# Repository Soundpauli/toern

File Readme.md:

# TŒRN `[tɜːn]`

**Open-source sequencer and sampler** — by [warft_ctrl](mailto:info@toern.live)

> Say it like *turn*. As in: turn the knobs. Turn a doodle into a beat. Turn “I can’t play piano” into “wait, that slap though.”

TŒRN is a sequenced musical device for beginners, makers, and anyone who likes blinking lights more than plugin menus. Think **Etch-A-Sketch™ energy**, but instead of drawing a wobbly staircase you draw drums, synths, and happy accidents — on a vivid **32×16 RGB LED panel** (standard; 16×16 optional) that is both the screen *and* the keyboard.

It sits on a Teensy 4.1, runs from a Micro SD card full of your WAVs, and is happy on a desk, in a backpack, or on battery at the park where strangers will ask “what *is* that?”

**Status:** under very active development. Things move fast. Stay tuned, and don’t be surprised if yesterday’s weird bug is today’s charming feature (or the other way around).

---

## What it is (in plain language)

You get:

- **8 sample voices** for drums, one-shots, loops, and “that weird recording from the metro”
- **1 three-voice polyphonic synth** with presets (bass, keys, chiptune, pads… the usual suspects)
- **2 monophonic synths** with LFO and arpeggiator for leads that refuse to sit still
- A **32-step × 8-page** sequencer (256 steps of room to overthink; 16×16 mode uses 16 steps × 16 pages), page chaining into songs, MIDI in/out, filters, bitcrush, reverb, and enough real-time knobs to keep your hands busy and your laptop jealous

No laptop required once it’s built. Samples live on the SD card. Patterns autosave. You twist, tap, and suddenly it’s 2 a.m.

For the friendly guided tour (first beat in about a minute), open the **[handbook](docs/handbook/index.html)** in this repo.

---

## A tiny history

TŒRN builds on the legacy of the **NI404**, with more features, fewer cables dangling off the side, and a custom PCB where everything mounts cleanly. The older “extra boards and hope” era is over.

Meet the glow-up:

- **RGB-I2C rotary encoders** — smoother, prettier, and they light up like they mean it
- **Custom PCB** — codec, charging, and jacks on one board
- **USB-C** — because micro-USB was a character-building experience we no longer need
- **LiPo charging port** — optional battery for true “make beats on a train” energy (battery not included; we trust you with electricity)
- **Proper audio I/O** — 6.35 mm headphone out, line in/out, mic in, *plus* a built-in mic for “sample the room right now” moments
- **TRS MIDI in/out** — play nice with the rest of your setup
- **On/off switch** — underrated luxury
- **Touch buttons** — for the things knobs shouldn’t monopolize
- **Laser-cut acrylic case** — files included; looks finished, not “breadboard cosplay”
- **JST connectors** — expansion leads plug in

Open source as always: schematics, code, and design files are here for you to poke, fork, and improve.

---

## Feature list

### Sequencer

- **11 instrument voices** on a 16-row grid: 8 sample voices (1–8), one 3-voice poly synth (11), two mono synths (13–14)
- Standard **32 steps per page × 8 pages** → 256 steps per pattern; optional 16×16 mode uses 16 steps × 16 pages
- **Voice mode**: each voice keeps its own pattern length. It loops the pages that hold its notes, pitches included, while the other voices keep looping on their own
- **FIRE** (ETC → ADV menu): optional playhead sparks when a chosen voice’s notes light white
- Store up to **999 patterns**, **999 samples**, **999 samplepacks**
- **Autosave / autoload** so your 3 a.m. genius doesn’t vanish at boot
- **Switch patterns live** without stopping playback
- **Song mode**: chain up to **64** page assignments from the current pattern
- Pattern ops: copy/paste, transpose page/channel (±1 octave), smart random notes (major/minor + rhythm ideas), clear page/channel
- **SWAP** exchanges notes between voices, with octave offsets; optional **SUBP** file subpatterns extend arrangements

### Sample voices (channels 1–8)

- Up to **~12 seconds** per voice at 44.1 kHz
- Browse and load samples **while playing** (yes, really)
- Per-voice start/end trim, forward/reverse
- **TIME** stretches or shortens samples independently of pitch
- Samplepacks (including pack 0 = custom per-voice assignment)
- Record from **built-in mic / line-in / mic-in** straight in the sample browser
- Save or merge used samples back to the SD card as a pack

### Synth voices

**Channel 11 — poly synth**

- 3 oscillators per voice × 3 voices
- Presets: BASS, KEYS, CHPT, PAD, WOW, ORG, FLT, LEAD, ARP, BRSS
- Per-voice ADSR, filter envelope, pan, volume, pitch (cents & semitones), waveform

**Channels 13–14 — mono synths**

- 2 oscillators each
- ADSR, LFO on cutoff/resonance, MIDI arpeggiator (step/span; does not pitch-shift grid notes)
- Waveforms: sine, saw, square, triangle

### Effects (all channels)

- **ADSR** — attack / decay / sustain / release (0–32 range)
- **Bitcrusher** — bit depth 1–16 (0 = bypass), sample-rate reduction down to glorious crunch
- **Filter** — LP / HP / BP, 0–10 kHz, resonance 0.7–5.0, smooth transitions
- **Reverb** — room size, damping, wet/dry; denser six-comb/four-diffuser network on reverb-equipped voices
- Fast filter access on encoder #3 during runtime (assignable default per channel)

### MIDI, clock & extras

- TRS MIDI in/out, clock send/receive, notes, transport
- BPM **40–300**, internal clock, external MIDI clock, tap tempo via touch
- Live recording / looping (touch-hold), up to ~12 s per voice
- Note probability, velocity, condition triggers (those “only every other bar” tricks)
- Global transpose, per-channel detune & octave, fine cents on the poly synth
- Mute / solo, pattern modes (OFF, ON, SONG, NEXT)
- Stereo routing options
- USB **Audio + Serial**: send the mix to a computer while using the SD tool; musical MIDI uses the TRS ports
- Analog clock **out (J25)**, clock **in (J26)** and voice-triggered **sidechain out (J27)**
- **TOUCHY** performance pads, live fills, and per-voice audition
- Browser tools for firmware flashing, SD transfers, sample conversion and the simulator
- **Demo animation:** open **ETC → INFO**, press **touch3 / BUTTON_C**; press and release **Touch 1 / BUTTON_A** to return to INFO

---

## Tech specs

| | |
|---|---|
| **Brain** | Teensy 4.1, PSRAM fitted. Audio codec is the SGTL5000 on the carrier |
| **Memory** | 16 MB PSRAM target; Micro SD (handbook suggests up to 64 GB, SanDisk Ultra) |
| **Audio** | 44.1 kHz, 16-bit mono WAV |
| **Controls** | 4× RGB illuminated I2C rotary-push encoders, 5 capacitive touch buttons |
| **Display** | Standard [32×16 RGB LED panel](https://de.aliexpress.com/item/1005010071864259.html), 512 LEDs (FastLED); 16×16 optional |
| **I/O** | 6.35 mm headphones, line in/out, mic in; built-in mic; TRS MIDI in/out |
| **Power** | USB-C or optional LiPo + charging |

---

## Repo map (where stuff lives)

| Path | Contents |
|------|----------|
| `platformio/` | Arduino sketch tabs, headers, custom audio in `src/`, build scripts and `platformio.ini` |
| `hardware/PCB/` | KiCad boards, schematics, manufacturing files and [purchasing BOMs](hardware/PCB/BOM/README.md) |
| `hardware/housing/` | Fusion archives, laser DXFs and panel previews |
| `docs/devdocs/` | Developer documentation → [docs.toern.live](https://docs.toern.live/) |
| `docs/handbook/` | Operator handbook → [handbook.toern.live](https://handbook.toern.live/) |
| `docs/BUILD.md`, `docs/info.md` | Hardware assembly and firmware build instructions |
| `tools/firmware/` | Browser firmware flasher (GPL-3.0) |
| `tools/sdtool/` | Browser SD tool |
| `tools/sim/` | Browser simulator |
| `tools/audioconvert/` | Standalone sample converter |
| `tools/case/` | Standalone case generator; `case.toern.live` planned, not deployed |
| `tools/colorsheme/`, `tools/_shared/` | Color editor and shared tool assets |
| `_debug/` | Host tests, analysis scripts and local diagnostic captures |
| `_private/` | Local business data/helpers; annotation tool in `_private/helpers/annotate/` |
| `website/` | Public project website only; local/deploy-only |

See [the complete directory map](docs/REPOSITORY_LAYOUT.md) for local-only items marked `***`.

Build from the repository root with `pio run -d platformio`, or `cd platformio` first.

For a personal hardware build, follow the [assembly and laser-cutting guide](docs/BUILD.md).
Start with the [BOM directory](hardware/PCB/BOM/README.md): check assembly-part stock
before ordering the PCB. The [pre-order list](hardware/PCB/BOM/preorder-parts.csv)
lists parts to secure for JLCPCB assembly. Then buy the
Teensy, PSRAM, encoders, matrix, cables and
case hardware separately. The website’s **Build** chapter covers the same assembly order.

---

## External libraries & modifications

This project leans on several libraries. Some are stock; some got lovingly (and necessary-ly) poked.

### Modified

- **ResamplingReader.h** (`teensy-variable-playback`)
  Variable rates, interpolation, multi-channel, loop types (repeat / ping-pong), crossfading — in `platformio/src/resamplerReader.h`

- **Treeverb** (`effect_treeverb`)
  Full-rate reverb with balanced 6/4 diffusion in RAM1 — `platformio/src/effect_treeverb.*`; the older `effect_freeverb_dmabuf` remains a host-test reference.

- **FastLED**
  `FASTLED_ALLOW_INTERRUPTS 0` so LEDs and audio don’t argue mid-beat; custom `FastLEDshow()` / `FastLEDclear()` wrappers

- **MIDI**
  Bigger Serial8 buffers for dense clock traffic (`RX 2048`, `TX 128`) and custom TRS MIDI settings

### Standard / upstream

- **TeensyPolyphony** by Nic Newdigate — polyphonic heart of the thing
- **Audio Library** (PJRC)
- **WS2812Serial**, **i2cEncoderLibV2**, **FastTouch**

---

## Get one

Order a TŒRN at **[toern.live](https://toern.live/)**. Questions go to **info@toern.live**.

When it arrives, open the **[handbook](docs/handbook/index.html)** and start at First beat. Power is USB-C. A battery and a microSD card are not in the parcel; the buy page and the handbook hardware chapter name what to get.

Firmware changes: [`info.md`](docs/info.md) to flash, [`docs/devdocs/`](docs/devdocs) for how the code is shaped, [`firmware-edits`](docs/devdocs/docs/contributing/firmware-edits.md) for a new menu page. Fabricating a board from the design files is [`BUILD.md`](docs/BUILD.md) — that is not how a TŒRN is ordered.

---

## License

- **Software / code**: [MIT](LICENSE) — free for personal and commercial use.
- **Firmware loader** (`tools/firmware/`): [GPL-3.0](tools/firmware/LICENSE), because that tool is Teensy Loader Javascript. GPL-3.0 applies only to that folder.
- **Hardware design files** (schematics, PCB layouts, Gerbers, housings, etc.): [CC BY-NC 4.0](https://creativecommons.org/licenses/by-nc/4.0/) — personal / non-commercial use and modification. **Jan-Peter Kuntoff is the only person authorized to sell TŒRN hardware** (bare PCB, assembled PCB, kit, or unit), including boards sold **without a Teensy**. Teensy 4.1 is PJRC’s; it is not licensed in this repo. Anyone else needs written consent to sell.

Commercial hardware licensing: Jan aka **warft_ctrl** — info@toern.live (Hamburg, Germany)

---

## Thank you

Huge thanks to **Paul Stoffregen** and the PJRC crew for Teensy, to the wider open-source audio community, and an especially loud shoutout to **Nic Newdigate** for teensy-polyphony — basically the soul of this project.

Made with too many late nights and exactly the right number of RGB LEDs.

**Jan aka warft_ctrl** (formerly soundpauli)
Hamburg, 2026

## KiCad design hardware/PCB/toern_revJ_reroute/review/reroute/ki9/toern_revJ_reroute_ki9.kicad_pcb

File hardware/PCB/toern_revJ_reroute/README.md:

# Toern revJ reroute

Open `toern_revJ_reroute.kicad_pro` with Backplane KiCad 10.99.0-bp.12.5. This is the archived partial reroute, with 22 nets changed. Its board format requires the newer editor. The original `../toern_revJ` is the stock KiCad 9.0.5 version restored from commit `ab3ea41`.

The [validation summary](review/reroute/validation-summary.md) records results and remaining USB and thermal work. The [pre-restore checkpoint](review/reroute/baseline) preserves the active revJ files from before the restore. The [Specctra session and KiCad 9 seed files](review/reroute/ki9) are an unverified transfer attempt.

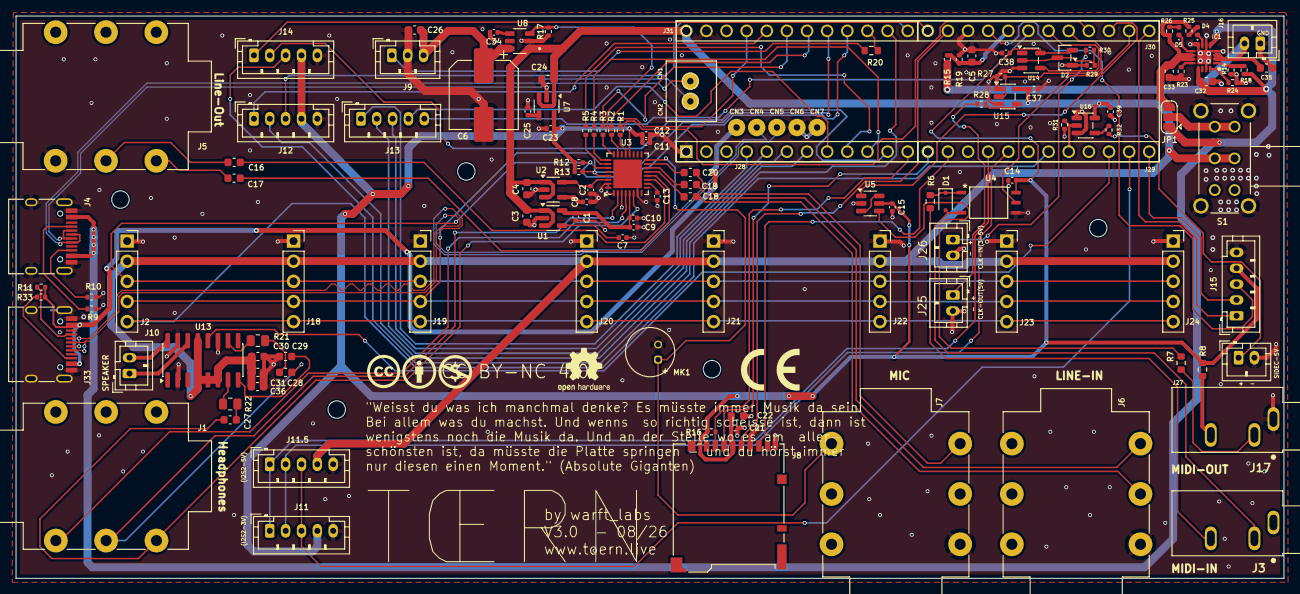
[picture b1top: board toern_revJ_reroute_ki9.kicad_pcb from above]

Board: 4 copper layers, 160.0 x 71.0 mm, 138 parts (0 on the bottom side), 109 nets.

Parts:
C1, C2, C9, C12, C23: 1u; C_0402_1005Metric
C3, C4, C16, C17, C18, C19, C20, C22, C24, C32: 10u; C_0603_1608Metric
C5, C26, C29: 100nF; C_0603_1608Metric
C6: 1000uF; CP_Elec_8x10.5
C7, C8, C25, C37, C38, C39: 100nF; C_0402_1005Metric
C10, C11, C14, C15, C21: 100n; C_0402_1005Metric
C13: 150n; C_0402_1005Metric
C27, C28: 0.47uF; C_0603_1608Metric
C30, C31: 1uF; C_0603_1608Metric
C33, C35: 4.7uF; C_0603_1608Metric
C34: 10nF; C_0402_1005Metric
C36: 22µF; C_0603_1608Metric
CN1, CN2: YZP0354-20100-01
CN3, CN4, CN5, CN6, CN7: YZP0354-20100-01; YZP0354-20100-01_Host
D1: BAT54J; D_SOD-323F
D2: BAT54S; SOT-23
D4: Red; LED_0402_1005Metric
D5: Yellow; LED_0402_1005Metric
IC1: BQ24075TRGTR; QFN50P300X300X100-17N-D
J1, J5, J6, J7: AudioJack3_Switch; Jack_6.35mm_Neutrik_NMJ6HCD2_Horizontal
J2, J18, J19, J20, J21, J22, J23, J24: Conn_01x05_Socket; PinSocket_1x05_P2.54mm_Vertical
J3, J17: AudioJack3_Ground; CUI_SJ1-3533
J4, J33: USB_C_Receptacle_USB2.0; USB_C_Receptacle_HRO_TYPE-C-31-M-12
J8: Micro_SD_Card; microSD_HC_Hirose_DM3BT-DSF-PEJS
J9: Conn_01x03; JST_PH_B3B-PH-K_1x03_P2.00mm_Vertical
J10, J16, J25, J26, J27: Conn_01x02; JST_PH_B2B-PH-K_1x02_P2.00mm_Vertical
J11, J11.5, J12, J13, J14, J15: Conn_01x05; JST_PH_B5B-PH-K_1x05_P2.00mm_Vertical
J28, J29, J30, J31: 929870-01-12-RA; 3M_929870-01-12-RA_Assembly
JP1: SolderJumper_3_Open; SolderJumper-3_P1.3mm_Open_RoundedPad1.0x1.5mm
LOGOOPENHARDWARE: OSHW-Logo2_7.3x6mm_SilkScreen
MK1: Microphone_Condenser; MIC-TH_BD6.0-P1.90-D0.4-L-FD
MountingHole1, MountingHole2, MountingHole3, MountingHole4, MountingHole5: MountingHole_2.2mm_M2
R1, R2, R3, R4, R5: 22R; R_0402_1005Metric
R6, R20: 220R; R_0603_1608Metric
R7, R8: 33R; R_0603_1608Metric
R9, R10: 5.1k; R_0402_1005Metric
R11, R33: 56k; R_0402_1005Metric
R12, R13, R16, R17: 10k; R_0402_1005Metric
R14: 49.9k; R_0402_1005Metric
R15: 1M; R_0402_1005Metric
R18: 200k; R_0402_1005Metric
R19: 1.5M; R_0402_1005Metric
R21, R22: 20k; R_0805_2012Metric
R23: 1.1k; R_0402_1005Metric
R24: 590R; R_0402_1005Metric
R25, R26: 1.5k; R_0402_1005Metric
R27, R29, R31: 100k; R_0402_1005Metric
R28, R32: 1k; R_0402_1005Metric
R30: 22k; R_0402_1005Metric
S1: EG2219
U1, U7: SPX3819M5-L-3-3; SOT-23-5
U2: SPX3819M5-L-1-8; SOT-23-5
U3: SGTL5000XNBA3; QFN-32-1EP_5x5mm_P0.5mm_EP3.6x3.6mm
U4: TLP2361V4_E; 5pin SO6_TOS
U5: 74LVC2G14; SOT-23-6
U6: Teensy4.1; Teensy41
U8: TPS22918DBVR; SOT95P280X145-6N
U13: PAM8403D; SOIC-16_3.9x9.9mm_P1.27mm
U14: 74LVC1G17; SOT-23-5
U15, U16: 74AHCT1G125; SOT-23-5

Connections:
2_OUT2: J13.1, U6.4 (2_OUT2)
3_LRCLK2: J13.3, U6.5 (3_LRCLK2)
4_BCLK2: J13.2, U6.6 (4_BCLK2)
5V-HOST: CN3.1 (CONTACT), J33.A4 (VBUS), J33.A9 (VBUS), J33.B4 (VBUS), J33.B9 (VBUS), R11.2, R33.2
5_IN2: J12.2, U6.7 (5_IN2)
6_OUT1D: J13.4, U6.8 (6_OUT1D)
7_RX2_OUT1A: R5.1, U6.9 (7_RX2_OUT1A)
8_TX2_IN1: R4.1, U6.10 (8_TX2_IN1)
9_OUT1C: J14.2, U6.11 (9_OUT1C)
10_CS_MQSR: J8.2 (DAT3/CD), R16.1, U6.12 (10_CS_MQSR)
11_MOSI_CTX1: J8.3 (CMD), U6.13 (11_MOSI_CTX1)
12_MISO_MQSL: J8.7 (DAT0), U6.14 (12_MISO_MQSL)
13_SCK_LED: J8.5 (CLK), U6.35 (13_SCK_LED)
14_A0_TX3_SPDIF_OUT: J14.1, U6.36 (14_A0_TX3_SPDIF_OUT)
15_A1_RX3_SPDIF_IN: J12.3, U6.37 (15_A1_RX3_SPDIF_IN)
16_A2_RX4_SCL1: J14.3, U6.38 (16_A2_RX4_SCL1)
17_A3_TX4_SDA1: R20.2, U6.39 (17_A3_TX4_SDA1)
18_A4_SDA: J2.3, J18.3, J19.3, J20.3, J21.3, J22.3, J23.3, J24.3, R12.2, U3.27 (CTRL_DATA), U6.40 (18_A4_SDA)
19_A5_SCL: J2.4, J18.4, J19.4, J20.4, J21.4, J22.4, J23.4, J24.4, R13.2, U3.29 (CTRL_CLK), U6.41 (19_A5_SCL)
20_A6_TX5_LRCLK1: R2.1, U6.42 (20_A6_TX5_LRCLK1)
21_A7_RX5_BCLK1: R3.1, U6.43 (21_A7_RX5_BCLK1)
22_A8_CTX1: J12.1, U6.44 (22_A8_CTX1)
23_A9_CRX1_MCLK1: R1.1, U6.45 (23_A9_CRX1_MCLK1)
24_A10_TX6_SCL2: J11.1, J11.5.1, U6.16 (24_A10_TX6_SCL2)
25_A11_RX6_SDA2: J11.2, J11.5.2, U6.17 (25_A11_RX6_SDA2)
27_A13_SCK1: J2.5, J18.5, J19.5, J20.5, J21.5, J22.5, J23.5, J24.5, U6.19 (27_A13_SCK1)
28_RX7: R31.2, U6.20 (28_RX7), U16.2
30_CRX3: U6.22 (30_CRX3), U13.12 (~SHDN)
31_CTX3: J11.3, J11.5.3, U6.23 (31_CTX3)
32_OUT1B: J15.2, U6.24 (32_OUT1B)
33_MCLK2: J15.1, U6.25 (33_MCLK2)
34_RX8: U4.5, U6.26 (34_RX8)
35_TX8: U5.1, U6.27 (35_TX8)
36_CS: R17.2, U6.28 (36_CS), U8.3 (ON)
37_CS: R27.2, U6.29 (37_CS), U15.2
38_CS1_IN1: U6.30 (38_CS1_IN1), U14.4
39_MISO1_OUT1A: J13.5, U6.31 (39_MISO1_OUT1A)
40_A16: C5.2, R15.2, R19.2, U6.32 (40_A16)
41_A17: J15.3, U6.33 (41_A17)
+1V8: C2.1, U2.5 (OUT), U3.30 (VDDD)
+3.3V: C11.1, C12.1, C14.2, C15.1, C21.2, C22.1, C23.1, C38.1, D2.2 (K), J8.4 (VDD), J11.4, J12.4, J14.4, J15.4, R8.2, R12.1, R13.1, R16.2, U3.20 (VDDIO), U4.6 (vcc), U5.5 (VCC), U7.5 (OUT), U14.5 (VCC)
+3.3VA: C1.1, C9.1, C10.1, U1.5 (OUT), U3.5 (VDDA)
+5V: C3.1, C4.1, C24.1, C30.2, C31.1, C36.1, C37.2, C39.2, J2.2, J11.5.4, J18.2, J19.2, J20.2, J21.2, J22.2, J23.2, J24.2, S1.2 (COM_1), S1.5 (COM_2), U1.1 (IN), U1.3 (EN), U2.1 (IN), U2.3 (EN), U6.48 (VIN), U7.1 (IN), U7.3 (EN), U8.1 (VIN), U13.4 (PVDD), U13.5 (~MUTE), U13.6 (VDD), U13.13 (PVDD), U15.5 (VCC), U16.5 (VCC)
D+: CN2.1 (CONTACT), J4.A6 (D+), J4.B6 (D+)
D+HOST: CN5.1 (CONTACT), J33.A6 (D+), J33.B6 (D+)
D-: CN1.1 (CONTACT), J4.A7 (D-), J4.B7 (D-)
D-HOST: CN4.1 (CONTACT), J33.A7 (D-), J33.B7 (D-)
GND: C1.2, C2.2, C3.2, C4.2, C5.1, C6.2, C7.2, C8.2, C9.2, C10.2, C11.2, C12.2, C13.2, C14.1, C15.2, C21.1, C22.2, C23.2, C24.2, C25.2, C26.2, C29.1, C30.1, C31.2, C32.2, C33.2, C34.2, C35.2, C36.2, C37.1, C38.2, C39.1, CN6.1 (CONTACT), CN7.1 (CONTACT), D2.1 (A), IC1.4 (~CE), IC1.6 (EN1), IC1.8 (VSS), IC1.15 (SYSOFF), IC1.17 (EP), J2.1, J4.A1 (GND), J4.A12 (GND), J4.B1 (GND), J4.B12 (GND), J4.S1 (SHIELD), J5.S, J6.S, J7.S, J8.6 (VSS), J8.9 (SHIELD), J9.2, J11.5, J11.5.5, J12.5, J14.5, J15.5, J16.1, J17.1, J18.1, J19.1, J20.1, J21.1, J22.1, J23.1, J24.1, J25.2, J26.2, J27.2, J33.A1 (GND), J33.A12 (GND), J33.B1 (GND), J33.B12 (GND), J33.S1 (SHIELD), MK1.2 (-), R9.2, R10.2, R14.2, R17.1, R19.1, R23.2, R24.2, R27.1, R29.1, R31.1, S1.MH1, S1.MH2, S1.MH3, S1.MH4, U1.2 (GND), U2.2 (GND), U3.1 (GND), U3.3 (GND), U3.7 (AGND), U3.31 (CTRL_ADR0_CS), U3.32 (CTRL_MODE), U3.33 (GND), U4.4 (gnd), U5.2 (GND), U6.1 (GND), U6.34 (GND), U6.47 (GND), U7.2 (GND), U8.2 (GND), U13.2 (PGND), U13.11 (GND), U13.15 (PGND), U14.3 (GND), U15.1, U15.3 (GND), U16.1, U16.3 (GND)
LINEIN_L: C19.2, U3.14 (LINEIN_L)
LINEIN_R: C18.2, U3.13 (LINEIN_R)
MIC: C20.2, U3.15 (MIC)
MICBIAS: J7.TN, MK1.1 (+), U3.16 (MIC_BIAS)
unnamed: C16.2, J5.R
unnamed: C17.2, J5.T
unnamed: C18.1, J6.R
unnamed: C19.1, J6.T
unnamed: C20.1, J7.T
unnamed: C27.2, R22.1
unnamed: C28.2, R21.1
unnamed: D1.2 (A), J3.2, U4.3
unnamed: D1.1 (K), R6.1, U4.1
unnamed: D2.3 (common), R29.2, R30.2, U14.2
unnamed: D4.2 (A), R25.1
unnamed: D4.1 (K), IC1.7 (~PGOOD)
unnamed: D5.2 (A), R26.1
unnamed: D5.1 (K), IC1.9 (~CHG)
unnamed: IC1.12 (ILIM), R23.1
unnamed: IC1.16 (ISET), R24.1
unnamed: IC1.1 (TS), R14.1, R18.1
unnamed: J3.3, R6.2
unnamed: J4.A5 (CC1), R9.1
unnamed: J4.B5 (CC2), R10.1
unnamed: J9.1, R20.1
unnamed: C6.1, C26.1, J9.3, U8.6 (VOUT)
unnamed: J10.1, U13.14 (ROUT-)
unnamed: J10.2, U13.16 (ROUT+)
unnamed: J17.2, R7.2
unnamed: J17.3, R8.1
unnamed: J25.1, R28.1
unnamed: J26.1, R30.1
unnamed: J27.1, R32.1
unnamed: J33.A5 (CC1), R11.1
unnamed: J33.B5 (CC2), R33.1
unnamed: JP1.2 (C), S1.3 (NO_1), S1.4 (NO_2)
unnamed: R7.1, U5.4
unnamed: R28.2, U15.4
unnamed: R32.2, U16.4
unnamed: C7.1, U1.4 (BP)
unnamed: C8.1, U2.4 (BP)
unnamed: C27.1, J1.T, U3.6 (HP_L)
unnamed: C28.1, J1.R, U3.2 (HP_R)
unnamed: J1.S, U3.4 (HP_VGND)
unnamed: R5.2, U3.26 (I2S_DIN)
unnamed: R4.2, U3.25 (I2S_DOUT)
unnamed: R2.2, U3.23 (I2S_LRCLK)
unnamed: R3.2, U3.24 (I2S_SCLK)
unnamed: C17.1, U3.12 (LINEOUT_L)
unnamed: C16.1, U3.11 (LINEOUT_R)
unnamed: R1.2, U3.21 (SYS_MCLK)
unnamed: C13.1, U3.10 (VAG)
unnamed: U5.3, U5.6
unnamed: C25.1, U7.4 (BP)
unnamed: C34.1, U8.4 (CT)
unnamed: R22.2, U13.7 (INL)
unnamed: R21.2, U13.10 (INR)
unnamed: C29.2, U13.8 (VREF)
VBAT: C35.1, IC1.2 (BAT_1), IC1.3 (BAT_2), J16.2, R15.1
VBUS: C32.1, IC1.5 (EN2), IC1.13 (IN), J4.A4 (VBUS), J4.A9 (VBUS), J4.B4 (VBUS), J4.B9 (VBUS), JP1.1 (A), R18.2
VYS: C33.1, IC1.10 (OUT_1), IC1.11 (OUT_2), JP1.3 (B), R25.2, R26.2

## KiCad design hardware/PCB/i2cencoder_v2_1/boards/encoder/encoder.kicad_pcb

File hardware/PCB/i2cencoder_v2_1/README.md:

# DuPPa I2C Encoder V2.1 for TŒRN

Open [encoder.kicad_pro](boards/encoder/encoder.kicad_pro) for the standalone four-layer KiCad project. The PCB preserves the DuPPa module outline, header and encoder drill geometry and adds a component-side TC2030-PKT-NL ICSP connection. See the [layout and validation report](review/layout.md) for the KiCad 9-format export, electrical checks and board renders.

The materials in [extra/upstream](extra/upstream) are pinned to DuPPa commit `d47fd5afe6d1130eee8f7d02c4856071b2adc8be`. They include the original hardware release and upstream license. Firmware source and both published HEX images are available through [pinned upstream links](extra/upstream/Firmware/README.md), rather than redistributed here. [DuPPa repository](https://github.com/DuPPadotnet/I2CEncoderV2.1/tree/d47fd5afe6d1130eee8f7d02c4856071b2adc8be) · [CircuitMaker project](https://workspace.circuitmaker.com/Projects/Details/Simone--Caron/I2C-Encoder-V2)

## Licensing

Hardware and the KiCad/ICSP modifications: **GPLv3**. Documentation: **CC BY-SA 4.0**. Original design by **DuPPa / Simone Caron**; TŒRN adaptations by Jan-Peter Kuntoff, recorded 2026-11-19. This folder is excluded from TŒRN’s MIT and noncommercial hardware defaults and exclusive-commercial-sale restriction. See [NOTICE.md](NOTICE.md) for attribution, modification details and license scope, and [LICENSE](LICENSE) for GPLv3.

## ICSP connector

Use the standard six-pad TC2030 no-legs pattern with the **TC2030-PKT-NL** cable for PICkit 3, 4 or 5. The TC2030-MCP-NL uses the same board geometry and ICSP assignment with an RJ12 programmer end. J1 implements the standard geometry on the component side with the numbered contacts connected as shown below. [Direct PICkit cable](https://www.tag-connect.com/product/tc2030-pkt-nl-6-pin-no-legs-cable-for-microchip-pickit-3) · [Tag-Connect pattern and wiring](https://www.tag-connect.com/wp-content/uploads/bsk-pdf-manager/2022/06/TC2030-MCP-NL.pdf)

| Pad | ICSP signal | DuPPa connection |
|---:|---|---|
| 1 | MCLR / VPP | U1 pin 1, RA3 / ADD3, MCU side of SJ4 |
| 2 | VDD target | U1 pin 18, VDD, MCU side of ferrite L1 |
| 3 | GND | U1 pin 17 and exposed pad GND net |
| 4 | PGD / ICSPDAT | U1 pin 16, RA0 / ADD0, MCU side of SJ1 |
| 5 | PGC / ICSPCLK | U1 pin 15, RA1 / ADD1, MCU side of SJ2 |
| 6 | AUX | Leave open |

J1 has three 0.9906 mm non-plated guide holes, six 0.7874 mm mask-open pads with no paste, and 1.27 mm contact spacing. The PCB has rule areas for the contact gap and nearby pours. The silkscreen dot identifies pin 1. Keep the module off the carrier while attaching the programming cable. [DuPPa hardware schematic and PCB drawing](https://github.com/DuPPadotnet/I2CEncoderV2.1/blob/master/Hardware/EncoderI2Cv2.1Layer.pdf) · [Microchip programming specification](https://ww1.microchip.com/downloads/aemDocuments/documents/OTH/ProductDocuments/ProgrammingSpecifications/40001738D.pdf)

## Flash sequence

A blank PIC16F18345 needs programming. Use MPLAB IPE with device PIC16F18345 and a PICkit, select the upstream [REV2.3 production HEX](https://github.com/DuPPadotnet/I2CEncoderV2.1/blob/d47fd5afe6d1130eee8f7d02c4856071b2adc8be/Firmware/Binary%20file%20REV2.3/I2CEncoderV2.1.X.production.hex), and program and verify flash and configuration words. Program with the module disconnected from the TŒRN carrier and with SJ1, SJ2 and SJ4 open. Power the target from one source and have the programmer reference the target VDD through pad 2. Use high-voltage ICSP, which is required to write the image's disabled LVP configuration. Set the address jumpers only after programming. Reopen any of SJ1, SJ2 or SJ4 that were closed before reprogramming the module.

Both upstream HEX files passed every Intel HEX record checksum and have LVP cleared in CONFIG3. The newer published REV2.3 file is the proposed first-article image. There has been no hardware flash or verification yet. [Upstream firmware notes](https://github.com/DuPPadotnet/I2CEncoderV2.1/tree/master/Firmware) · [Microchip programming specification](https://ww1.microchip.com/downloads/aemDocuments/documents/OTH/ProductDocuments/ProgrammingSpecifications/40001738D.pdf)

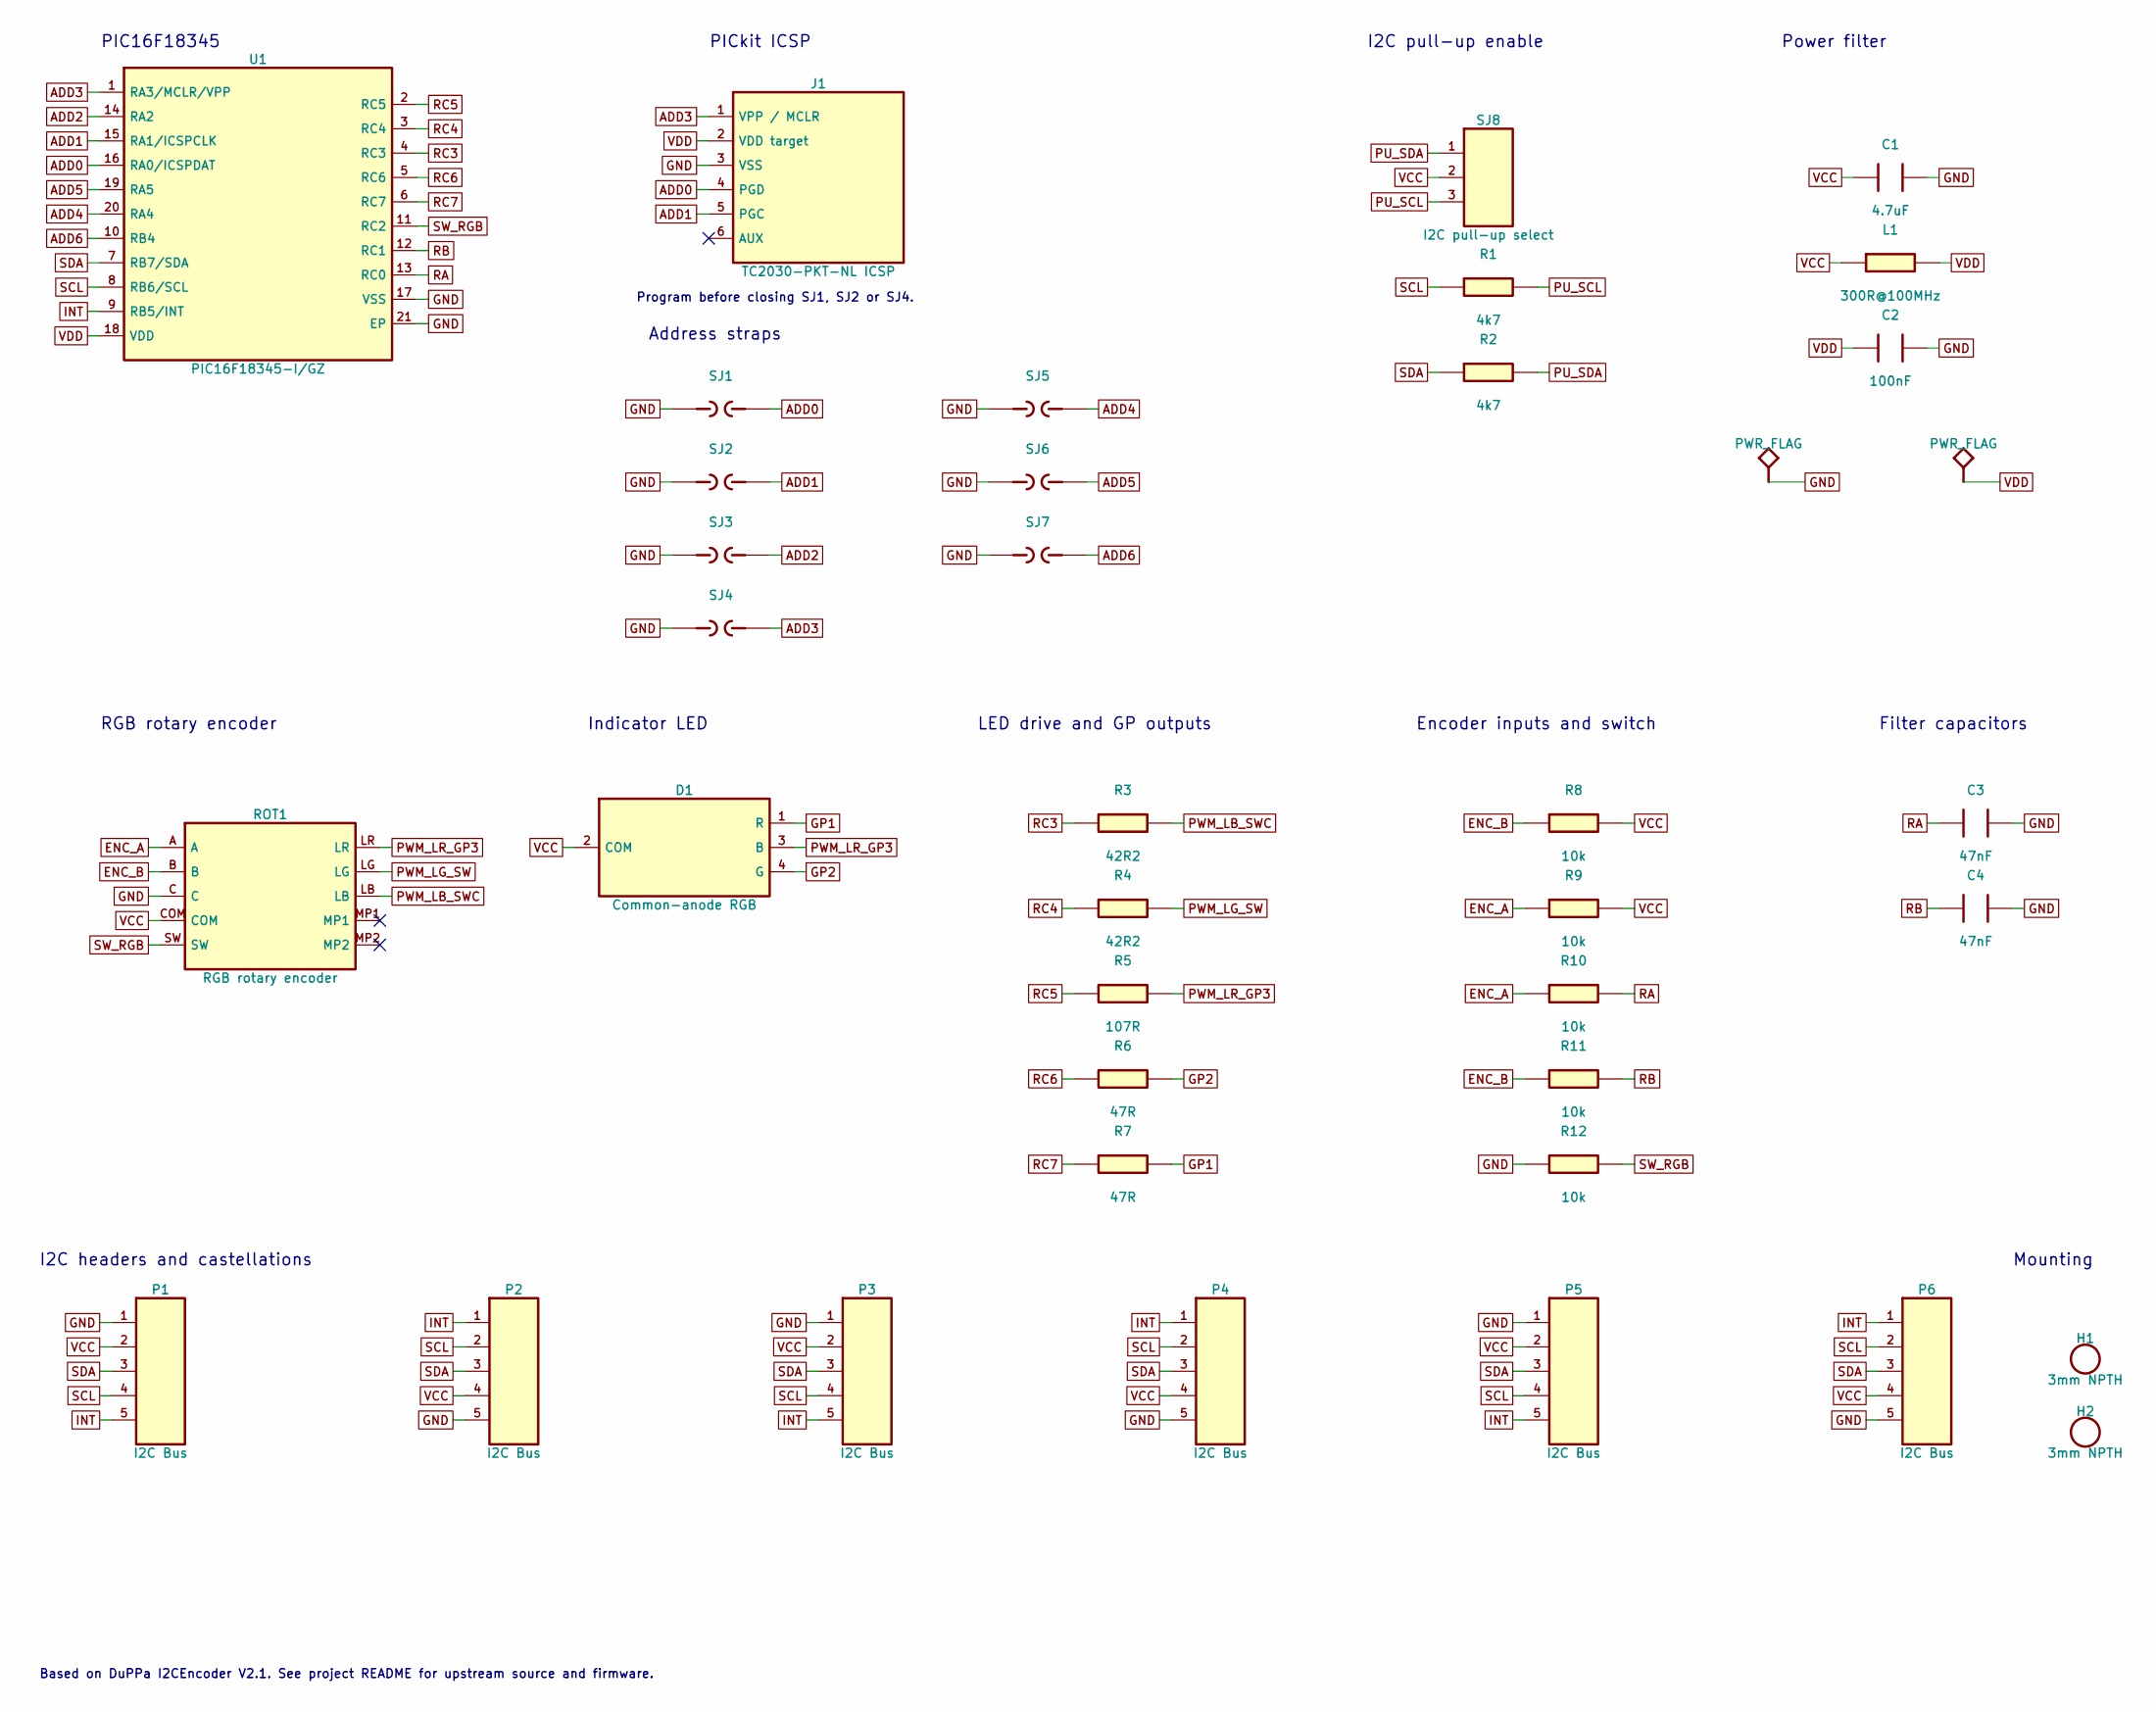
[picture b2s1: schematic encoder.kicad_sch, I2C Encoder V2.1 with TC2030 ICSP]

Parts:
C1: 4.7uF; C1_DuPPa; MPN CC0603KRX5R7BB475
C2: 100nF; C2_DuPPa; MPN GRM155R61C104KA88D
C3: 47nF; C3_DuPPa; MPN GCM155R71E473KA55D
C4: 47nF; C4_DuPPa; MPN GCM155R71E473KA55D
D1: Common-anode RGB; D1_DuPPa
H1: 3mm NPTH; H1_DuPPa
H2: 3mm NPTH; H2_DuPPa
J1: TC2030-PKT-NL ICSP; TC2030-PKT-NL
L1: 300R@100MHz; L1_DuPPa; MPN ACML-0402HC-301T
P1: I2C Bus; P1_DuPPa
P2: I2C Bus; P2_DuPPa
P3: I2C Bus; P3_DuPPa
P4: I2C Bus; P4_DuPPa
P5: I2C Bus; P5_DuPPa
P6: I2C Bus; P6_DuPPa
R1: 4k7; R1_DuPPa; MPN RC0402FR-074K7L
R2: 4k7; R2_DuPPa; MPN RC0402FR-074K7L
R3: 42R2; R3_DuPPa; MPN AC0402FR-0742R2L
R4: 42R2; R4_DuPPa; MPN AC0402FR-0742R2L
R5: 107R; R5_DuPPa; MPN RC0402FR-07107RL
R6: 47R; R6_DuPPa; MPN RC0402FR-0747RL
R7: 47R; R7_DuPPa; MPN RC0402FR-0747RL
R8: 10k; R8_DuPPa; MPN RC0402FR-0710KL
R9: 10k; R9_DuPPa; MPN RC0402FR-0710KL
R10: 10k; R10_DuPPa; MPN RC0402FR-0710KL
R11: 10k; R11_DuPPa; MPN RC0402FR-0710KL
R12: 10k; R12_DuPPa; MPN RC0402FR-0710KL
ROT1: RGB rotary encoder; ROT1_DuPPa
SJ1: Address strap; SJ1_DuPPa
SJ2: Address strap; SJ2_DuPPa
SJ3: Address strap; SJ3_DuPPa
SJ4: Address strap; SJ4_DuPPa
SJ5: Address strap; SJ5_DuPPa
SJ6: Address strap; SJ6_DuPPa
SJ7: Address strap; SJ7_DuPPa
SJ8: I2C pull-up select; SJ8_DuPPa
U1: PIC16F18345-I/GZ; U1_DuPPa; MPN PIC16F18345-I/GZ

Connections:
ADD0: J1.4 (PGD), SJ1.2, U1.16 (RA0/ICSPDAT)
ADD1: J1.5 (PGC), SJ2.2, U1.15 (RA1/ICSPCLK)
ADD2: SJ3.2, U1.14 (RA2)
ADD3: J1.1 (VPP / MCLR), SJ4.2, U1.1 (RA3/MCLR/VPP)
ADD4: SJ5.2, U1.20 (RA4)
ADD5: SJ6.2, U1.19 (RA5)
ADD6: SJ7.2, U1.10 (RB4)
ENC_A: R9.1, R10.1, ROT1.A
ENC_B: R8.1, R11.1, ROT1.B
GND: C1.2, C2.2, C3.2, C4.2, J1.3 (VSS), P1.1, P2.5, P3.1, P4.5, P5.1, P6.5, R12.1, ROT1.C, SJ1.1, SJ2.1, SJ3.1, SJ4.1, SJ5.1, SJ6.1, SJ7.1, U1.17 (VSS), U1.21 (EP)
GP1: D1.1 (R), R7.2
GP2: D1.4 (G), R6.2
INT: P1.5, P2.1, P3.5, P4.1, P5.5, P6.1, U1.9 (RB5/INT)
PU_SCL: R1.2, SJ8.3
PU_SDA: R2.2, SJ8.1
PWM_LB_SWC: R3.2, ROT1.LB
PWM_LG_SW: R4.2, ROT1.LG
PWM_LR_GP3: D1.3 (B), R5.2, ROT1.LR
RA: C3.1, R10.2, U1.13 (RC0)
RB: C4.1, R11.2, U1.12 (RC1)
RC3: R3.1, U1.4 (RC3)
RC4: R4.1, U1.3 (RC4)
RC5: R5.1, U1.2 (RC5)
RC6: R6.1, U1.5 (RC6)
RC7: R7.1, U1.6 (RC7)
SCL: P1.4, P2.2, P3.4, P4.2, P5.4, P6.2, R1.1, U1.8 (RB6/SCL)
SDA: P1.3, P2.3, P3.3, P4.3, P5.3, P6.3, R2.1, U1.7 (RB7/SDA)
SW_RGB: R12.2, ROT1.SW, U1.11 (RC2)
VCC: C1.1, D1.2 (COM), L1.1, P1.2, P2.4, P3.2, P4.4, P5.2, P6.4, R8.2, R9.2, ROT1.COM, SJ8.2
VDD: C2.1, J1.2 (VDD target), L1.2, U1.18 (VDD)

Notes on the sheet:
PIC16F18345
PICkit ICSP
Address straps
I2C pull-up enable
Power filter
RGB rotary encoder
Indicator LED
LED drive and GP outputs
Encoder inputs and switch
Filter capacitors
I2C headers and castellations
Mounting
Program before closing SJ1, SJ2 or SJ4.
Based on DuPPa I2CEncoder V2.1. See project README for upstream source and firmware.

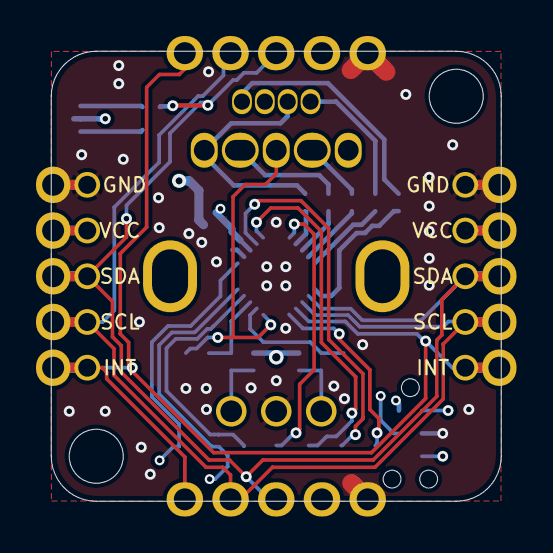
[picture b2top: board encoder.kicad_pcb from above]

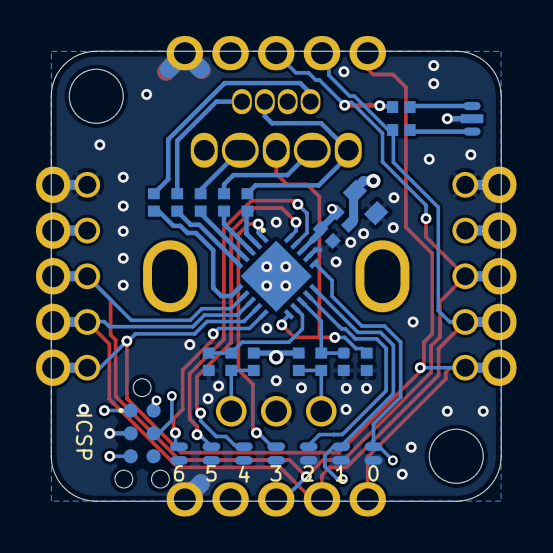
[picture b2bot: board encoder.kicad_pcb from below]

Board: 4 copper layers, 25.0 x 25.0 mm, 37 parts (27 on the bottom side), 30 nets.

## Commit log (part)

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2025-01-27 added MIDI-IN
2025-02-03 starting adsr implementation + bugfixing
2025-02-04 bugfixes for playback and filebrowser
2025-02-07 cleaning up files
2025-02-13 fixed bug with posString
2025-02-17 fixed sample-splicing
2025-02-26 added UI for filters
2025-02-28 splitted main files to clean
2025-03-19 added filters for V13
2025-03-19 completed synth integration 11-14
2025-03-24 added drums for ch1-3
2025-03-25 fixed filters and bugfixes plus menu
2025-03-28 Update LICENSE
    Changed HW license to CC by nc
2025-03-28 fixed sample loading and editing
2025-03-29 fixed midi In Clock
2025-03-29 fixed midi in and out
2025-03-30 fixed midi
2025-04-04 added multi osc and drums for ch1-4
2025-04-06 fixed memory issues
2025-04-08 fixed ram problems
2025-04-11 further fixed for filters and voices
2025-04-16 more fixes for synths and freqs
2025-04-24 more bugfixes and features
2025-04-26 fixed sample cutting
2025-04-29 fixed sampler and midi + ui
2025-05-07 additional bugfixes
2025-05-11 bugfixes and delay timings
2025-05-20 added touch and realtime recording
2025-05-23 fixed BPM calculations for midi
2025-05-23 fixed midi transport
2025-05-24 fixed settings and menu
2025-05-26 added fast-recording via 3.5mm pedal
2025-06-17 fixed playback and midi
2025-06-17 fixed wav selection
2025-06-18 added PMOD patternmode
2025-07-07 flattend audio setup, fixed bugs with memory during play
2025-07-15 new filter views
2025-08-21 bugfixes
2025-09-11 further bugfixes
2025-09-13 added AI
2025-09-18 bugfixes and added filters
2025-09-19 bugfixes for encoderlights and midi
2025-09-26 added subpattern mode
2025-10-04 more bugfixes and some features
2025-10-18 fixing samplepack saving
2025-10-18 fixing sampl search and midi mode
2025-10-18 added reverse samples
2025-10-18 added bugfixes for ai
2025-10-21 cleanup and new menu, songmode
2025-10-21 cleanup and new menu, songmode2
2025-10-22 added probabilies
2025-10-22 added probabilies fix
2025-10-22 added fix for multiple panels
2025-10-23 adding fixes for eepromcrash
2025-10-25 fixed reset and memory
2025-10-28 back to working version after memory/pong fail
2025-11-07 fixed recording
2025-11-08 memory opt and bugfixes
2025-11-08 memory opt and bugfixes2
2025-11-09 added PONG
2025-11-09 PONG fixes
2025-11-11 added CTRL mode play/vol
2025-11-15 fixed midi sync
2025-11-15 fixed midi sync and transport
2025-11-19 matze hat geregelt - midi läuft
2025-11-20 looper recording fixed
2025-11-25 fixed midi finally
2025-11-25 fixed midi finally + autosave fix
2025-11-26 added condition triggers
2025-11-26 added condition triggers - advanced
2025-11-26 fixed fastfilters
2025-11-26 fixed button debounce 30ms ghostplaypause
2025-11-27 fixed button debounce 30ms ghostplaypause 2
2025-11-27 changes in monitoring-in
2025-11-27 changes in monitoring-in 2
2025-11-28 changes for bpm, rec and helpers
2025-11-30 fixed memory issues with large samples
2025-12-01 fixed overflows on long runs
2025-12-06 fixes for ram1, freeverbs and more
2025-12-06 fixes for ch11 fastfilter
2025-12-06 fixes for midi channels and loudness
2025-12-06 fixed synth voices, removed DRUMS
2025-12-06 added LFO and ARPEGGIATOR ch13+14
2025-12-14 performance fix and filenames
2025-12-14 syth filter and defaults deeper
2025-12-15 UX bugfixes
2025-12-15 auto generation for NEW
2025-12-18 added alternatie draw method
2025-12-22 further fixes for menu
2025-12-27 fixed samplebrowsing for large files
2025-12-27 fixed samplerates
2025-12-27 added Channel splitting 1-4,5-8
2025-12-27 fix for ch11 bounds
2025-12-28 added error logging to sd2
2026-01-07 added play on touch
2026-01-07 fixed menu
2026-01-07 various bugfixes
2026-01-09 fixes in soundquality
2026-01-23 varoious fixes in stability
2026-01-23 reverted some fixes again
2026-01-23 fixed timer display flickering
2026-01-26 custom color shemes
2026-01-26 fixed sample preview and loader
2026-01-26 fixed sample preview and loader2
2026-02-20 various fixes
2026-02-20 clean up
2026-02-20 updated readme and info
2026-02-20 clean up kiCad Files
2026-02-20 pcb: locking unmovable parts
2026-02-20 pcb: fixing thermal relief
2026-03-02 more fixes
2026-03-09 fixes for HD Displays 32x16
2026-03-12 extended reverb and muteAll fix for Draw==R
2026-03-12 fixed PCB and shematics for RevG
2026-03-12 fixed PCB and shematics for RevG 2
2026-03-13 fixed brightnesssettings on load and save
2026-03-13 fixed menu exitpaths
2026-03-13 fixed menu and filter touch crashes
2026-03-13 fixed folder display
2026-03-17 fix drawmode==r
2026-03-17 pre-menu commit
2026-03-17 fix for sampledirection and mutes
2026-03-17 change of menu encoders
2026-03-17 better midi-in sync workflow
2026-03-17 fix for midi sync external transport
2026-03-18 fix serialColorRead()
2026-03-19 miditransport delay menu
2026-03-19 pre-memory test
2026-03-20 fixed instruments
2026-03-21 pre browser
2026-03-22 new filebrowser
2026-03-22 fixed ch13+14 noteoff
2026-03-23 check midi
2026-03-23 fixed midi ch13+14 release
2026-03-23 fixed ch13+14 filters+pass defaults
2026-03-23 fix startup ch13+14 dmamem error
2026-03-23 fix long press ch11
2026-03-23 fix instruments ADSR
2026-03-23 fixed CRF settings for ch11
2026-03-23 fixed midi input ch13+14
2026-03-24 freed more ram1 via pagetmp array
2026-03-24 cleaned up vars
2026-03-24 checkpoint further cleanups
2026-03-24 fixed pitch for c13+14
2026-03-24 samplesize colors
2026-03-24 added gain headroom: max 6 voices in parallel, adjustable)
2026-03-26 better loading and saving speed and progress
2026-03-27 screensaver and HFC
2026-03-27 global Mutes revisited
2026-04-08 pre-plan:sync issues
2026-04-25 finalizing firmware
2026-05-06 changed name
2026-05-06 small fixes in code, additional TPS22918DBVR for PCB (leds)
2026-05-09 fixed audio/pack loading and handling, also added eyes screensaver
2026-05-09 fixed defaults for eeprom
2026-05-11 fixed PCB: right resistors for TS + componentsize
2026-05-11 fixed PCB: right resistors for TS + componentsize - final
2026-05-18 included childMode for easy play:thank you miniBooth
2026-05-21 fixed battery display and final bugfixes for 2.2
